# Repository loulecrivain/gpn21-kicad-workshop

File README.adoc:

= KiCad Workshop Handout
Evils <evils.devils@protonmail.com>
:homepage: https://gitlab.com/evils/kicad-workshop
:license: CERN-OHL-W-2.0
:keywords: KiCad, workshop, handout, learn, schematic, capture, PCB, printed, circuit, board, layout, design, EDA, suite, DIY, electronics
:toc2:
:sectanchors:
:sectlinks:
:hardbreaks:
:hide-uri-scheme:

This handout is intended to be used in conjunction with an instructor giving a KiCad workshop.
It is based on cpresser's MCH2022 handout and should be valid for KiCad version 7.
This repo contains the source .odt file which embeds the D-DIN font it uses.
Plus a link:./handout.pdf[.pdf] and link:./handout.png[.png] render of that.
And the KiCad source for the example schematic.

image::handout.png[]

== Additional materials
An older, elaborate workshop outline can be found in the `cmoy` branch here {homepage}.

notes:
first place the components in the schematic
then assign the footprints with the BOM tool (top right corner of toolbar)

use erc (electrical rule check) to verify there's no generator-generator connection (bad !!!)

use shift+space to change from hard angle to no angle in wiring mode

then open pcb design and press F8 to import the schematic to the pcb. you now have to do the routing by hand

move the parts with m, flip to bottom with f, rotate with r, wire with x

DRC -> checklist "exécuter les règles de vérification de pcb"

then file > gerber export > trace and open the .grbj (gerber job) with the integrated kicad gerber viewer

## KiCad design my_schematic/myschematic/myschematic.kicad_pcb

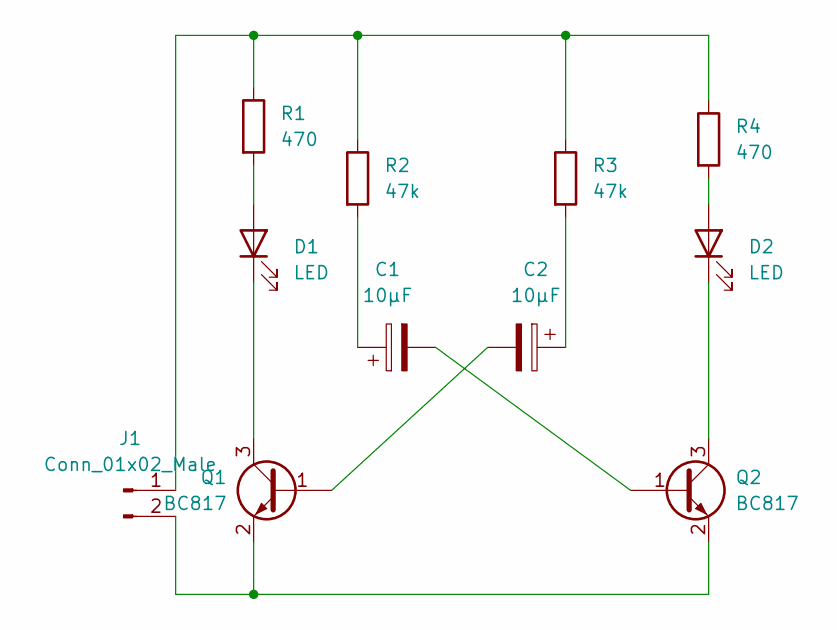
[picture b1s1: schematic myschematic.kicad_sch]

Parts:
C1, C2: 10µF; C_0805_2012Metric_Pad1.18x1.45mm_HandSolder
D1, D2: LED; LED_0805_2012Metric_Pad1.15x1.40mm_HandSolder
J1: Conn_01x02_Male; PinHeader_1x02_P2.00mm_Vertical
Q1, Q2: BC817; SOT-23
R1, R4: 470; R_0805_2012Metric_Pad1.20x1.40mm_HandSolder
R2, R3: 47k; R_0805_2012Metric_Pad1.20x1.40mm_HandSolder

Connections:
unnamed: C1.1, R2.2
unnamed: C2.1, R3.2
unnamed: C2.2, Q1.1 (B)
unnamed: J1.2, Q1.2 (E), Q2.2 (E)
unnamed: D1.1 (K), Q1.3 (C)
unnamed: C1.2, Q2.1 (B)
unnamed: D2.1 (K), Q2.3 (C)
unnamed: J1.1, R1.1, R2.1, R3.1, R4.1
unnamed: D1.2 (A), R1.2
unnamed: D2.2 (A), R4.2

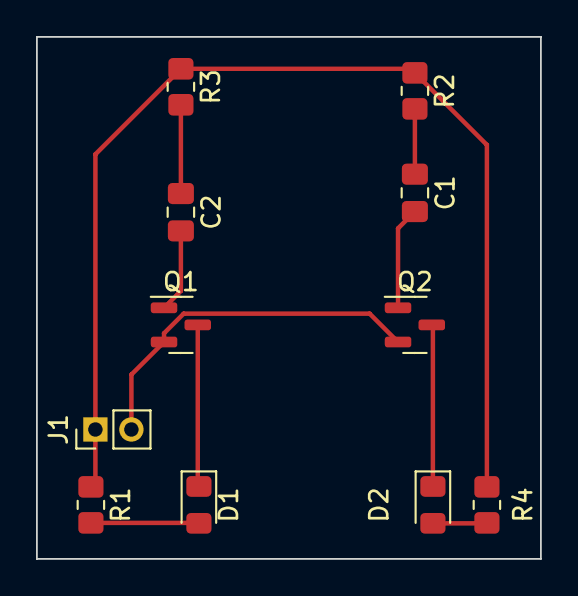
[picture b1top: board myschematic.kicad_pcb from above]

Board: 2 copper layers, 28.0 x 29.0 mm, 11 parts (0 on the bottom side), 10 nets.

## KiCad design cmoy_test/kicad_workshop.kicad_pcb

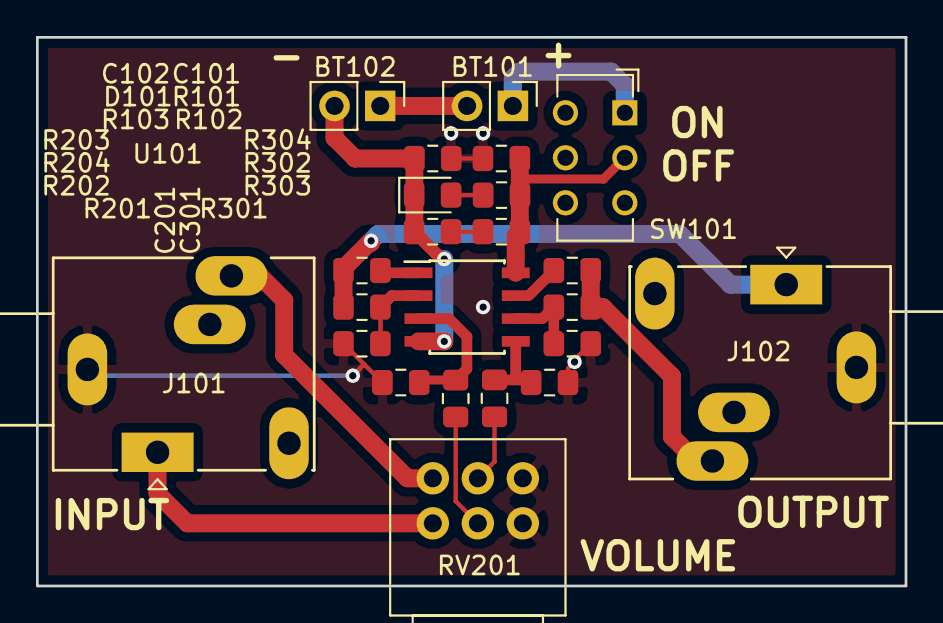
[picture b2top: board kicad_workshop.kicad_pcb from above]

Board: 2 copper layers, 48.3 x 30.5 mm, 23 parts (0 on the bottom side), 19 nets.

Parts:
BT101, BT102: Battery_Cell; PinHeader_1x02_P2.54mm_Vertical
C101, C102: CP1_Small; C_0805_2012Metric_Pad1.15x1.40mm_HandSolder
C201, C301: C_Small; C_0805_2012Metric_Pad1.15x1.40mm_HandSolder
D101: LED; LED_0805_2012Metric_Pad1.15x1.40mm_HandSolder
J101, J102: AudioJack3; Jack_3.5mm_Ledino_KB3SPRS_Horizontal
R101, R102, R103, R201, R202, R203, R204, R301, R302, R303, R304: R_Small; R_0805_2012Metric_Pad1.15x1.40mm_HandSolder
RV201: R_POT_Dual_Separate; Potentiometer_Alps_RK097_Dual_Horizontal
SW101: SW_SPST; SW_CuK_JS202011CQN_DPDT_Straight
U101: Opamp_Dual_Generic; SOIC-8_3.9x4.9mm_P1.27mm

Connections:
+9V: C101.1, R101.1, R102.1, SW101.2, U101.8
-9V: BT102.2, C102.2, D101.1, R103.2, U101.4
/cmoy_channel/IN: J101.T, RV201.1
/cmoy_channel/OUT: J102.T, R203.1, R204.2
/sheet5C71BC7F/IN: J101.R, RV201.4
/sheet5C71BC7F/OUT: J102.R, R303.1, R304.2
Earth: C101.2, C102.1, J101.S, J102.S, R201.2, R202.2, R301.2, R302.2, RV201.3, RV201.6
unnamed: BT101.1, SW101.1
unnamed: BT101.2, BT102.1
unnamed: C201.1, R201.1, U101.3
unnamed: C201.2, RV201.2
unnamed: C301.1, R301.1, U101.5
unnamed: C301.2, RV201.5
unnamed: D101.2, R101.2
unnamed: R102.2, R103.1
unnamed: R202.1, R203.2, U101.2
unnamed: R204.1, U101.1
unnamed: R302.1, R303.2, U101.6
unnamed: R304.1, U101.7

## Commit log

2019-03-03 start
2019-03-13 expand README.md
2019-03-27 add license
2021-09-05 add link to proto_amp for the falstad simulation
2021-09-05 separate proto_amp link from previous quote
2023-02-15 switch to cpresser's handout
2023-02-15 link to the pdf and png files
2023-02-20 embed schematic (almost) directly from KiCad
2023-02-20 cleanup embedded fonts
2023-02-20 cleanup Makefile
2023-02-20 fix timestamp in kicad-cli output
2023-02-20 fix pdf reproducibility as well
    2000 because libreoffice doesn't seem to like 1970
2023-03-25 minor rephrasing
    fix a typo
    fix justification of schematic text
2023-03-25 call swriter instead of libreoffice
2023-06-10 workflow instructions
2023-06-10 schematic, pcb design & routing, gerber exporgt
